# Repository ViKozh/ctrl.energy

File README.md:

# ctrl.energy
 ESPHome-based node for energy monitoring with additional functionality

## Brief Description
 This module made for my own house as main power meter sensor and gate / outdoor lights control. There're two ESP32 nodes on PCB. One of them performs energy meter monitoring via RS-485 / MODBUS interface. Another one is used to control sliding gates control with Wiegand-based keys and outdoor lights. Also it monitors gate state.

## Hardware
 IMPORTANT!!! Working with HOT LINE AC is dangerous and could harm or even kill! Don't do anything if you don't know how it could behave.
 IMPORTANT 2!!! This hardware works from DC12 power source (J2). It can commutate 5 channels of 16A 230AC via K2-K5 relays.

 You can view PCB and schematic in the _/hardware_ folder in this repository. It was made in KiCAD, so you don't need to buy expensive PCB toolkit to modify or view it. Just keep in mind following mistakes (not the only these, I suppose):
  - Incorrect placements for reed switch based relays (K7 and K8). I've found this error only when recieved produced PCBs - so I decided not to fix it.
  - You'll need better heatsink. LM1084-3.3 could be very hot when powered by 12V. So you should use good thermal interface for it.

 *Note*: PCB successfully soldered and working well (it works almost two weeks.)

## Capabilities

### Energy control node:
  - Temperature monitoring in House Energy Box via D18B20 sensor (J1).
  - Monitor UPS state: battery health (binary sensor) and main power source state (binary sensor) (J3).
  - Monitor state of main power circuit breaker (J4) with auxilary contact like [this](https://automationforum.co/what-is-auxiliary-contact-and-how-it-works-with-mcb/).
  - Monitor case intrusion to House Energy Box via switch connected to J6.
  - Writing logs and settings to microSD card module (J18).
  - Integrated ds3232 RTC clock (EEPROM and alarms functionality is currently not supported by ESPHome) + cr2032 lithium battery.
  - Modbus / RS485 interface via RS485 to UART converter (J12).
  - UART logs from ESP32 (J9).
  - Power Control for Gate control node to reduce power consumption when Main Power source is off the grid.
  - Send messages of problems, daily and monthly report via Telegram Bot (you should create it, see Telegram bot reference to know how to create own telegram bot).

### Gate control node:
  - Control sliding gates in two modes (i.e. full open mode and pedestrian mode) (J16).
  - Sense gate state (opened or closed) with any switch or button (J17).
  - Stores up to 8 Wiegand-26 keys to open gate - use *+ KEY* (SW3) to add a new key, short press *- KEY* (SW4) to remove one key, long press *- KEY* to remove all keys from memory of ESP32.
  - RFID (Wiegand-26 protocol) with J15 pins 5-8.
  - Indicates success or failure with red/green LEDs (J15, pins 2 and 3 as control _ground pins_, pin 1 as +12V power pin for LEDs)
  - Controls up to 5 lamps/zones (*HOT ZONE!!! Up to AC 230v*) - connect AC power source to J5, connect lamps to J7, J8, J10, J11 and J13.

## Configuration

### Energy control node:

  You should configure _secrets.yaml_ to use telegram bot. Both *tg_token_id* and *tg_chat_id* are required for messaging. 

  Set *pincode* to define code to arm/disarm case intrusion protection.

  Set *energy_provider_name* to you Energy Company name or anything else.

  Set *ha_url* to your Home Assistant instance URL and *grafana_url* to Grafana Dashboard. This links will be available in telegram messages.

  Another options are pretty common for ESPHome configs. See _config.yaml_ for all required variables.

### Gate control node:

  This node configuration is also contains common for ESPHome secret variables.

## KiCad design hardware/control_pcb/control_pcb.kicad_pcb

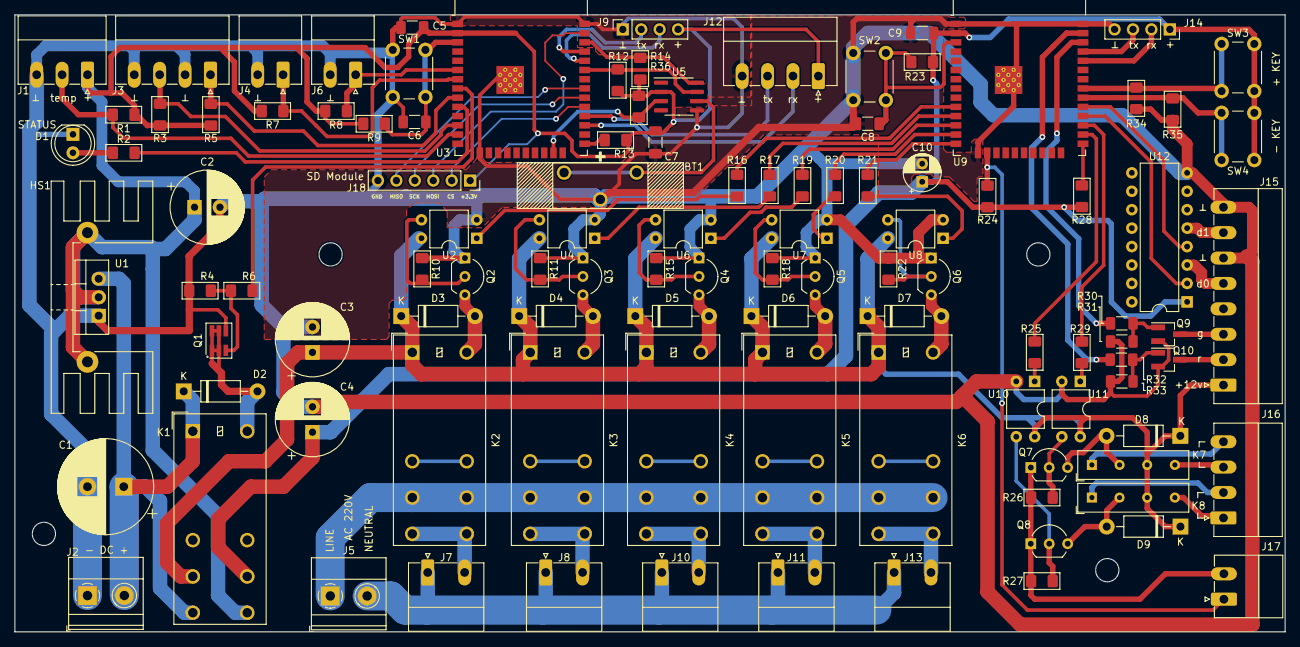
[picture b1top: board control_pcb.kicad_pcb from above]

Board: 2 copper layers, 175.0 x 85.0 mm, 109 parts (0 on the bottom side), 85 nets.

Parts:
BT1: CR2032; Battery_Holder_CR2032_Vertical
C1: 1000uF / 50v; CP_Radial_D13.0mm_P5.00mm
C2, C4: 100uF / 16v; CP_Radial_D10.0mm_P3.50mm
C3: 100uF / 50v; CP_Radial_D10.0mm_P3.50mm
C5, C7, C9: 100nF; C_1206_3216Metric_Pad1.33x1.80mm_HandSolder
C6, C8: 1uF; C_1206_3216Metric_Pad1.33x1.80mm_HandSolder
C10: 10uF / 16v; CP_Radial_D5.0mm_P2.50mm
D1: STATUS; LED_D5.0mm_Clear
D2: 1N4002; D_DO-41_SOD81_P10.16mm_Horizontal
D3, D4, D5, D6, D7, D8, D9: 1N4007; D_DO-41_SOD81_P10.16mm_Horizontal
HS1: Heatsink_Pad; Heatsink_Stonecold_HS-132_32x14mm_2xFixation1.5mm
J1: DS18B20 TEMP; PhoenixContact_MC_1,5_3-G-3.5_1x03_P3.50mm_Horizontal
J2: DC12v; TerminalBlock_Phoenix_MKDS-1,5-2-5.08_1x02_P5.08mm_Horizont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
J3: UPS_DETECTION; PhoenixContact_MC_1,5_4-G-3.5_1x04_P3.50mm_Horizontal
J4: INPUT_FUSE_SENSE; PhoenixContact_MC_1,5_2-G-3.5_1x02_P3.50mm_Horizontal
J5: AC IN; TerminalBlock_Phoenix_MKDS-1,5-2-5.08_1x02_P5.08mm_Horizont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
J6: CASE_SENSOR; PhoenixContact_MC_1,5_2-G-3.5_1x02_P3.50mm_Horizontal
J7: Parking; PhoenixContact_MC_1,5_2-G-5.08_1x02_P5.08mm_Horizontal
J8: Front Yard; PhoenixContact_MC_1,5_2-G-5.08_1x02_P5.08mm_Horizontal
J9: EC_RS232; PinSocket_1x04_P2.54mm_Vertical
J10: Bollards; PhoenixContact_MC_1,5_2-G-5.08_1x02_P5.08mm_Horizontal
J11: Address; PhoenixContact_MC_1,5_2-G-5.08_1x02_P5.08mm_Horizontal
J12: MODBUS_UART; PhoenixContact_MC_1,5_4-G-3.5_1x04_P3.50mm_Horizontal
J13: Fence Lights; PhoenixContact_MC_1,5_2-G-5.08_1x02_P5.08mm_Horizontal
J14: LC_RS232; PinSocket_1x04_P2.54mm_Vertical
J15: RFID_READER; PhoenixContact_MC_1,5_8-G-3.5_1x08_P3.50mm_Horizontal
J16: GATES_CONTROL; PhoenixContact_MC_1,5_4-G-3.5_1x04_P3.50mm_Horizontal
J17: GATES_STATE_SWITCH; PhoenixContact_MC_1,5_2-G-3.5_1x02_P3.50mm_Horizontal
J18: SD Module; PinSocket_1x06_P2.54mm_Vertical
K1: G2RL-2; Relay_DPDT_Omron_G2RL-2
K2, K3, K4, K5, K6: G2RL-1-E; Relay_SPDT_Omron_G2RL-1-E
K7, K8: EDR101A1200; Relay_SPST_StandexMeder_MS_Form1AB
Q1: AO6400; SOT-23-6_Handsoldering
Q2, Q3, Q4, Q5, Q6, Q7, Q8: 2N2222; TO-92_Inline_Wide
Q9, Q10: IRLML2402; SOT-23_Handsoldering
R1: 4k7; R_1206_3216Metric_Pad1.42x1.75mm_HandSolder
R2: 68; R_1206_3216Metric_Pad1.42x1.75mm_HandSolder
R3, R4, R5, R7, R8, R9, R10, R11, R12, R13, R14, R15, R18, R22, R23, R24, R26, R27, R28, R34, R35, R36: 10k; R_1206_3216Metric_Pad1.42x1.75mm_HandSolder
R6: 150; R_1206_3216Metric_Pad1.42x1.75mm_HandSolder
R16, R17, R19, R20, R21, R25, R29: 120; R_1206_3216Metric_Pad1.42x1.75mm_HandSolder
R30, R32: 1k; R_1206_3216Metric_Pad1.30x1.75mm_HandSolder
R31, R33: 100k; R_1206_3216Metric_Pad1.30x1.75mm_HandSolder
SW1: EC_RESET; SW_PUSH_6mm
SW2: GLC_RESET; SW_PUSH_6mm
SW3: Write Token; SW_PUSH_6mm
SW4: Delete Token; SW_PUSH_6mm
U1: LM1084-3.3; TO-220-3_Vertical
U2, U4, U6, U7, U8, U10, U11: PC817; DIP-4_W7.62mm
U3, U9: ESP32-WROOM-32; ESP32-WROOM-32D
U5: DS3232M; SOIC-8_3.9x4.9mm_P1.27mm
U12: DIP-16_W7.62mm

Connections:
/+3.3V: C4.1, C9.2, C10.1, J14.1, K1.21, R23.2, R24.1, R28.1, SW3.2, SW4.2, U9.2 (VDD), U12.1 (Vdd)
/+3.3V_PROTECTED: C2.1, C5.2, C7.2, HS1.1, J1.1, J9.4, J12.1, J18.1, K1.24, R1.1, R3.2, R5.2, R7.2, R8.2, R9.2, R12.2, R13.1, R14.2, R36.1, U1.2 (VO), U3.2 (VDD), U5.2 (VCC)
/+12V: C3.1, D3.1 (K), D4.1 (K), D5.1 (K), D6.1 (K), D7.1 (K), D8.1 (K), D9.1 (K), J15.1, K1.11, K2.A1, K3.A1, K4.A1, K5.A1, K6.A1, K7.5, K8.5, U2.4, U4.4, U6.4, U7.4, U8.4, U10.4, U11.4
/Energy Control/AC_LOW: J3.3, R3.1, U3.12 (IO27)
/Energy Control/BAT_LOW: J3.1, R5.1, U3.9 (IO33)
/Energy Control/CASE_OPEN: J6.1, R8.1, U3.6 (IO34)
/Energy Control/EC_M_RX: J12.2, U3.27 (IO16)
/Energy Control/EC_M_TX: J12.3, U3.28 (IO17)
/Energy Control/EC_RX: J9.3, U3.34 (RXD0/IO3)
/Energy Control/EC_TX: J9.2, U3.35 (TXD0/IO1)
/Energy Control/INPUT_FUSE: J4.1, R7.1, U3.7 (IO35)
/Energy Control/INT_TEMP: J1.2, R1.2, U3.13 (IO14)
/Energy Control/SCL: R14.1, U3.36 (IO22), U5.8 (SCL)
/Energy Control/SDA: R12.1, U3.33 (IO21), U5.7 (SDA)
/Energy Control/SD_CS: J18.2, U3.29 (IO5)
/Energy Control/SD_MISO: J18.5, U3.31 (IO19)
/Energy Control/SD_MOSI: J18.3, U3.37 (IO23)
/Energy Control/SD_SCK: J18.4, U3.30 (IO18)
/Energy Control/TACT_FREQ: R36.2, U3.23 (IO15), U5.3 (~INT/SQW)
/LIGHT_00: R16.1, U9.10 (IO25)
/LIGHT_01: R17.1, U9.11 (IO26)
/LIGHT_02: R19.1, U9.12 (IO27)
/LIGHT_03: R20.1, U9.13 (IO14)
/LIGHT_04: R21.1, U9.14 (IO12)
/Lights Relays/LINE: J5.1, K2.11, K3.11, K4.11, K5.11, K6.11
/Lights Relays/NEUTRAL: J5.2, J7.1, J8.1, J10.1, J11.1, J13.1
/OPEN_GATE: R25.2, U9.26 (IO4)
/OPEN_PEDS: R29.2, U9.27 (IO16)
/POW_CTRL: R6.1, U3.8 (IO32)
/SENS_GATE: J17.1, R24.2, U9.16 (IO13)
/WD_0: U9.28 (IO17), U12.2 (Out_A)
/WD_1: U9.29 (IO5), U12.4 (Out_B)
/WLED_GREEN: R30.1, U9.36 (IO22)
/WLED_RED: R32.1, U9.37 (IO23)
/Wiegand Converter/LED_CTRL_GREEN: J15.3, Q9.3 (D)
/Wiegand Converter/LED_CTRL_RED: J15.2, Q10.3 (D)
/Wiegand Converter/WIEGAND_D0: J15.5, U12.3 (In_A)
/Wiegand Converter/WIEGAND_D1: J15.7, U12.5 (In_B)
GND: BT1.2 (-), C1.2, C2.2, C3.2, C4.2, C5.1, C6.2, C7.1, C8.2, C9.1, C10.2, D1.1 (K), J1.3, J2.1, J3.2, J3.4, J4.2, J6.2, J9.1, J12.4, J14.4, J15.6, J15.8, J17.2, J18.6, Q1.4 (S), Q2.1 (E), Q3.1 (E), Q4.1 (E), Q5.1 (E), Q6.1 (E), Q7.1 (E), Q8.1 (E), Q9.2 (S), Q10.2 (S), R4.2, R10.1, R11.1, R15.1, R18.1, R22.1, R26.2, R27.2, R31.1, R33.1, R34.1, R35.1, SW1.1, SW2.1, U1.1 (GND), U2.2, U3.1 (GND), U3.15 (GND), U3.38 (GND), U3.39 (GND), U4.2, U5.5 (GND), U6.2, U7.2, U8.2, U9.1 (GND), U9.15 (GND), U9.38 (GND), U9.39 (GND), U10.2, U11.2, U12.8 (Vss)
unnamed: BT1.1 (+), U5.6 (VBAT)
unnamed: D1.2 (A), R2.1
unnamed: D2.2 (A), K1.A2, Q1.1 (D), Q1.2 (D), Q1.5 (D), Q1.6 (D)
unnamed: C1.1, D2.1 (K), J2.2, K1.14, K1.A1, U1.3 (VI)
unnamed: D3.2 (A), K2.A2, Q2.3 (C)
unnamed: D4.2 (A), K3.A2, Q3.3 (C)
unnamed: D5.2 (A), K4.A2, Q4.3 (C)
unnamed: D6.2 (A), K5.A2, Q5.3 (C)
unnamed: D7.2 (A), K6.A2, Q6.3 (C)
unnamed: D8.2 (A), K7.3, Q7.3 (C)
unnamed: D9.2 (A), K8.3, Q8.3 (C)
unnamed: J7.2, K2.14
unnamed: J8.2, K3.14
unnamed: J10.2, K4.14
unnamed: J11.2, K5.14
unnamed: J13.2, K6.14
unnamed: J14.2, U9.34 (RXD0/IO3)
unnamed: J14.3, U9.35 (TXD0/IO1)
unnamed: J16.1, K8.7
unnamed: J16.2, K8.1
unnamed: J16.3, K7.7
unnamed: J16.4, K7.1
unnamed: Q1.3 (G), R4.1, R6.2
unnamed: Q2.2 (B), R10.2, U2.3
unnamed: Q3.2 (B), R11.2, U4.3
unnamed: Q4.2 (B), R15.2, U6.3
unnamed: Q5.2 (B), R18.2, U7.3
unnamed: Q6.2 (B), R22.2, U8.3
unnamed: Q7.2 (B), R26.1, U11.3
unnamed: Q8.2 (B), R27.1, U10.3
unnamed: Q9.1 (G), R30.2, R31.2
unnamed: Q10.1 (G), R32.2, R33.2
unnamed: R16.2, U2.1
unnamed: R17.2, U4.1
unnamed: R19.2, U6.1
unnamed: R20.2, U7.1
unnamed: R21.2, U8.1
unnamed: R25.1, U10.1
unnamed: R29.1, U11.1
unnamed: C6.1, R9.1, SW1.2, U3.3 (EN)
unnamed: R13.2, U3.25 (IO0)
unnamed: R2.2, U3.10 (IO25)
unnamed: C8.1, R23.1, SW2.2, U9.3 (EN)
unnamed: R28.2, U9.25 (IO0)
unnamed: R35.2, SW4.1, U9.30 (IO18)
unnamed: R34.2, SW3.1, U9.31 (IO19)

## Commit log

2024-03-05 Ready for testing
    Implemented core functionality for ESP32-based node
2024-03-05 Added supplemental projects and updated README
2024-03-11 Various fixes after testing
    I've made a lot of fixes after testing on the working prototype of hardware.
2024-03-12 Settings has been moved to internal memory
    Fixed logic for select component though it seems to work unexpectable.
2024-03-13 Fix to min/max monitoring and total power failure duration.
2024-03-14 Fixed logic for problems handling
